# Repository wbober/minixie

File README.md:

minixie
=======

This project is my take on creating a simple Nixie tube clock. The design uses few
components but packs some nice features.

Features
--------
* a real time clock with super cap backup
* a buzzer
* a light intensity sensor
* an auxiliary connector (UART, IRQ, GPIO, +5V)
* support for an optional DCF77 decoder

Hardware
--------
* only 3 ICs (7805, ATMega8, and 74141 driver)
* single side PCBs
* through-hole components
* designed for LC531 tubes
* small size (46x108mm)
* EagleCAD source for schematics and PCB

Software
--------
* written in C
* tested with AVRStudio/Eclipse

License
-------
Copyright (c) 2012-2014 Wojciech Bober
Licensed under the GNU GPL v2 license

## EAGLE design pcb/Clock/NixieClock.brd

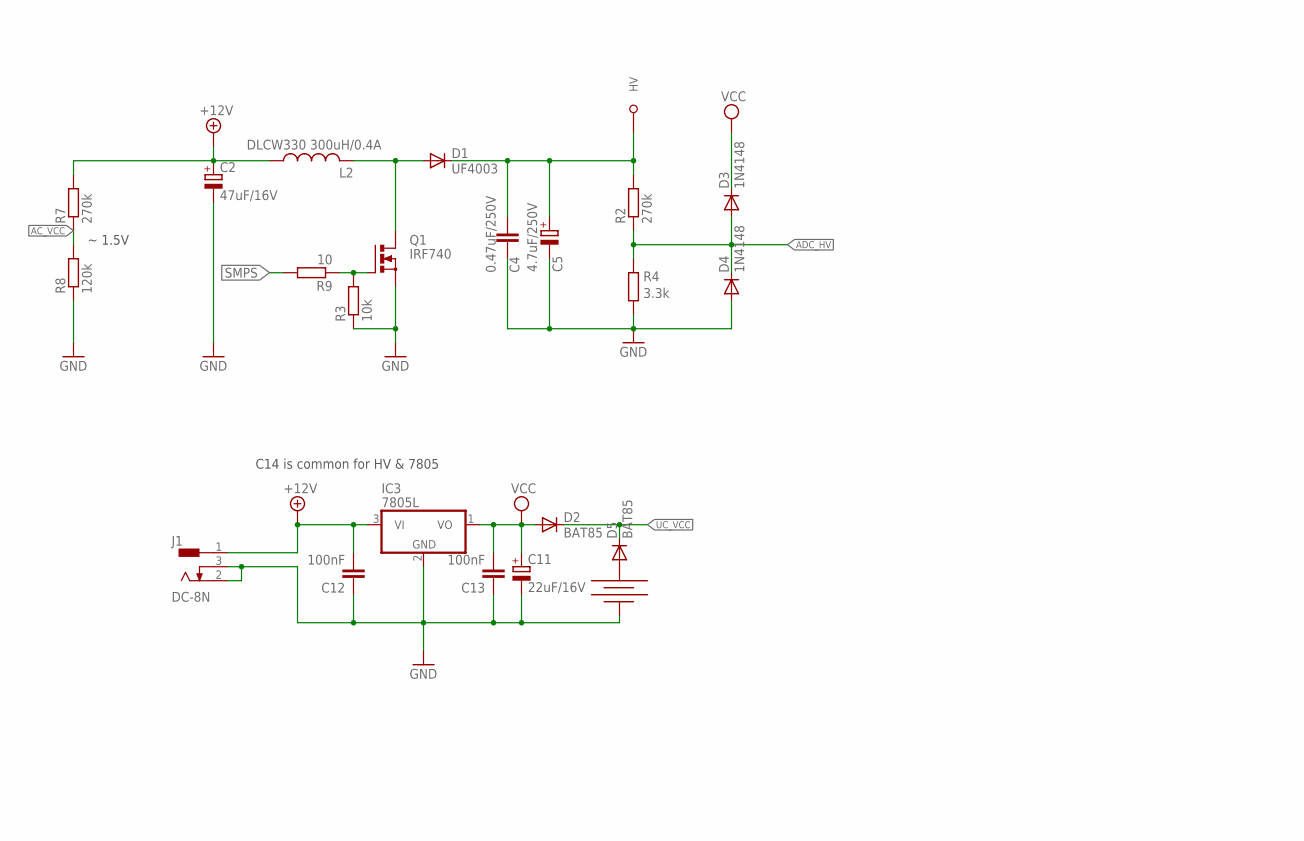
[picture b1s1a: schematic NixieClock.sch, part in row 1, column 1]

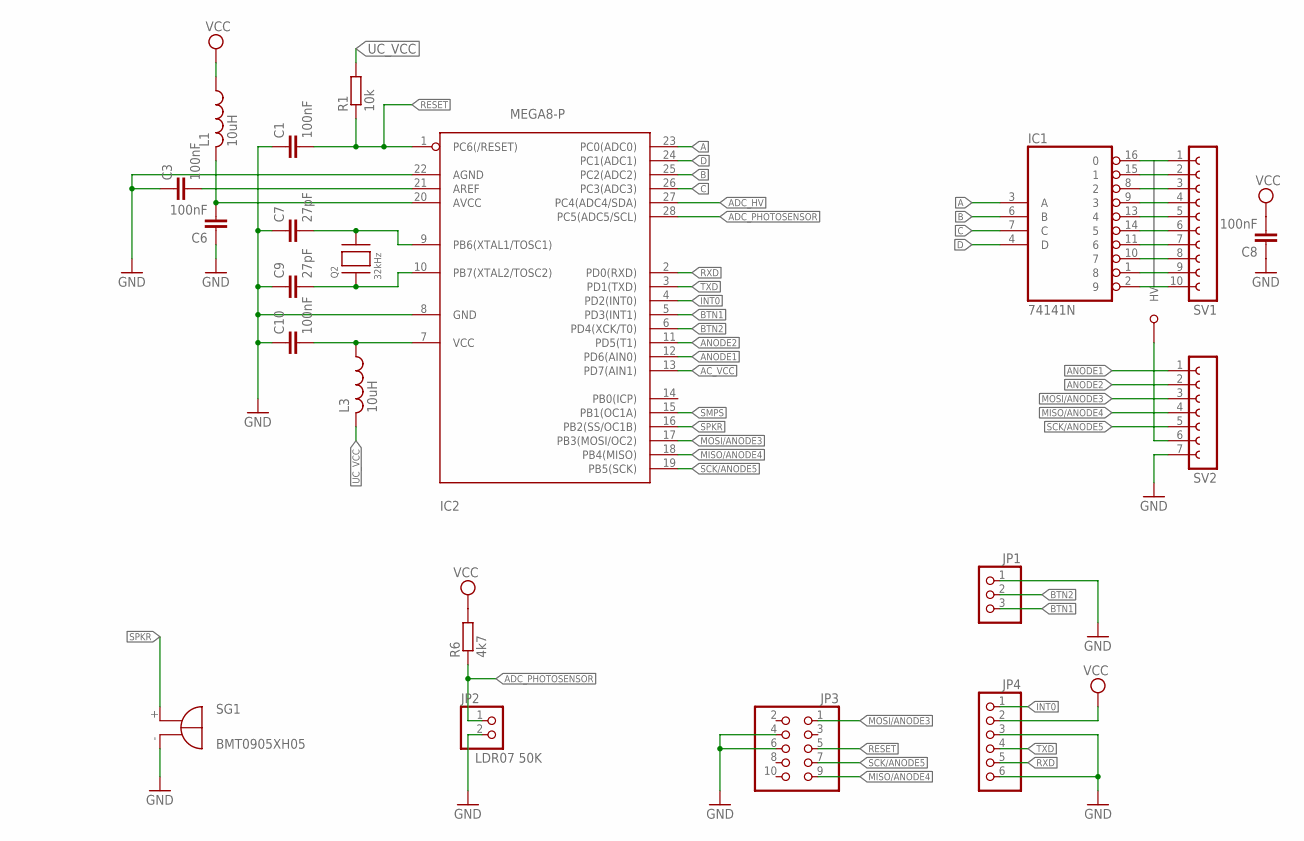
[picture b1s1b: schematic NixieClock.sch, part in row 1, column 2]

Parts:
C1, C3, C6, C10, C12, C13: 100nF; C025-025X050
C2: 47uF/16V; E2,5-7
C4: 0.47uF/250V; C10B6
C5: 4.7uF/250V; CAP_RADIAL
C7, C9: 27pF; C025-025X050
C8: 100nF; C050-025X075
C11: 22uF/16V; E2,5-6
D1: UF4003; DO41-10
D2, D5: BAT85; DO35-7
D3, D4: 1N4148; DO35-7
IC1: 74141N; DIL16
IC2: MEGA8-P; DIL28-3
IC3: 7805L; TO92
J1: DC-8N
JP1: PINHD-1X3/90; 1X03/90
JP2: LDR07 50K; 1X02
JP3: PINHD-2X5/90; 2X05/90
JP4: PINHD-1X6/90; 1X06/90
L1: 10uH; 0204/7
L2: DLCW330 300uH/0.4A; MURATA-CHOKE-7-4
L3: 10uH; 0204/5
Q1: IRF740; TO220BH
Q2: 32kHz; QS
R1: 10k; 0207/12
R2, R7: 270k; 0204/5
R3: 10k; 0204/5
R4: 3.3k; 0204/5
R6: 4k7; 0204/5
R8: 120k; 0204/5
R9: 10; 0204/5
SG1: BMT0905XH05
SV1: FE10-1; FE10
SV2: FE07-1; FE07
U$3: BAT1220THT; 1220

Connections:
+12V: C2.+, C12.2, IC3.3 (VI), J1.1, L2.P$1 (1), R7.2
A: IC1.3 (A), IC2.23 (PC0(ADC0))
AC_VCC: IC2.13 (PD7(AIN1)), R7.1, R8.2
ADC_HV: D3.A, D4.C, IC2.27 (PC4(ADC4/SDA)), R2.1, R4.2
ADC_PHOTOSENSOR: IC2.28 (PC5(ADC5/SCL)), JP2.1, R6.1
ANODE1: IC2.12 (PD6(AIN0)), SV2.1
ANODE2: IC2.11 (PD5(T1)), SV2.2
B: IC1.6 (B), IC2.25 (PC2(ADC2))
BTN1: IC2.5 (PD3(INT1)), JP1.3
BTN2: IC2.6 (PD4(XCK/T0)), JP1.2
C: IC1.7 (C), IC2.26 (PC3(ADC3))
D: IC1.4 (D), IC2.24 (PC1(ADC1))
D1: IC1.2 (9), SV1.1
D2: IC1.1 (8), SV1.2
D3: IC1.16 (0), SV1.3
D4: IC1.15 (1), SV1.4
D5: IC1.14 (5), SV1.5
D6: IC1.13 (4), SV1.6
D7: IC1.11 (6), SV1.7
D8: IC1.10 (7), SV1.8
D9: IC1.9 (3), SV1.9
D10: IC1.8 (2), SV1.10
GND: C1.1, C2.-, C3.1, C4.2, C5.P$4 (-), C6.1, C7.1, C8.1, C9.1, C10.1, C11.-, C12.1, C13.1, D4.A, IC1.12 (GND), IC2.8 (GND), IC2.22 (AGND), IC3.2 (GND), J1.2, J1.3, JP1.1, JP2.2, JP3.4, JP3.6, JP4.3, JP4.6, Q1.S, R3.1, R4.1, R8.1, SG1.-, SV2.7, U$3.-
HV: C4.1, C5.P$3 (+), D1.C, R2.2, SV2.6
INT0: IC2.4 (PD2(INT0)), JP4.1
MISO/ANODE4: IC2.18 (PB4(MISO)), JP3.9, SV2.4
MOSI/ANODE3: IC2.17 (PB3(MOSI/OC2)), JP3.1, SV2.3
unnamed: C7.2, IC2.9 (PB6(XTAL1/TOSC1)), Q2.P$2
unnamed: C9.2, IC2.10 (PB7(XTAL2/TOSC2)), Q2.P$1
unnamed: D5.A, U$3.+
unnamed: Q1.G, R3.2, R9.1
unnamed: C6.2, IC2.20 (AVCC), L1.2
unnamed: C10.2, IC2.7 (VCC), L3.1
unnamed: C3.2, IC2.21 (AREF)
unnamed: D1.A, L2.P$2 (2), Q1.D
RESET: C1.2, IC2.1 (PC6(/RESET)), JP3.5, R1.1
RXD: IC2.2 (PD0(RXD)), JP4.5
SCK/ANODE5: IC2.19 (PB5(SCK)), JP3.7, SV2.5
SMPS: IC2.15 (PB1(OC1A)), R9.2
SPKR: IC2.16 (PB2(SS/OC1B)), SG1.+
TXD: IC2.3 (PD1(TXD)), JP4.4
UC_VCC: D2.C, D5.C, L3.2, R1.2
VCC: C8.2, C11.+, C13.2, D2.A, D3.C, IC1.5 (VCC), IC3.1 (VO), JP4.2, L1.1, R6.2

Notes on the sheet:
C14 is common for HV & 7805
~ 1.5V

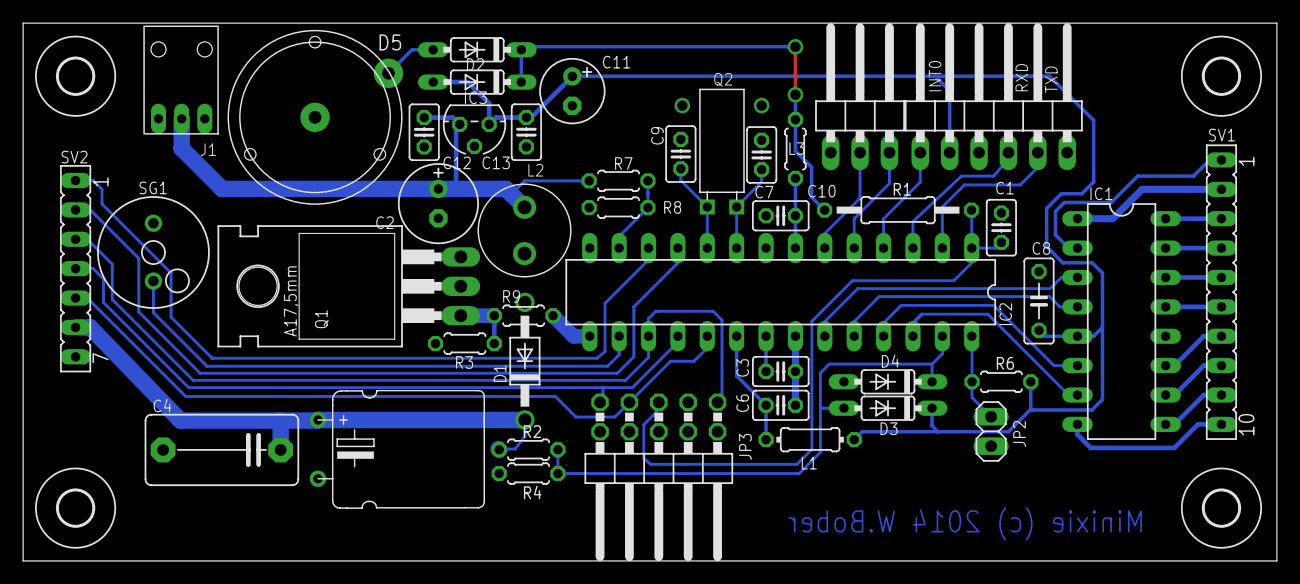
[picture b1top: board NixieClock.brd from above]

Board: 2 copper layers, 108.4 x 46.5 mm, 47 parts (0 on the bottom side), 43 nets.

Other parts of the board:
U$5, U$6, U$7, U$8: 3,0

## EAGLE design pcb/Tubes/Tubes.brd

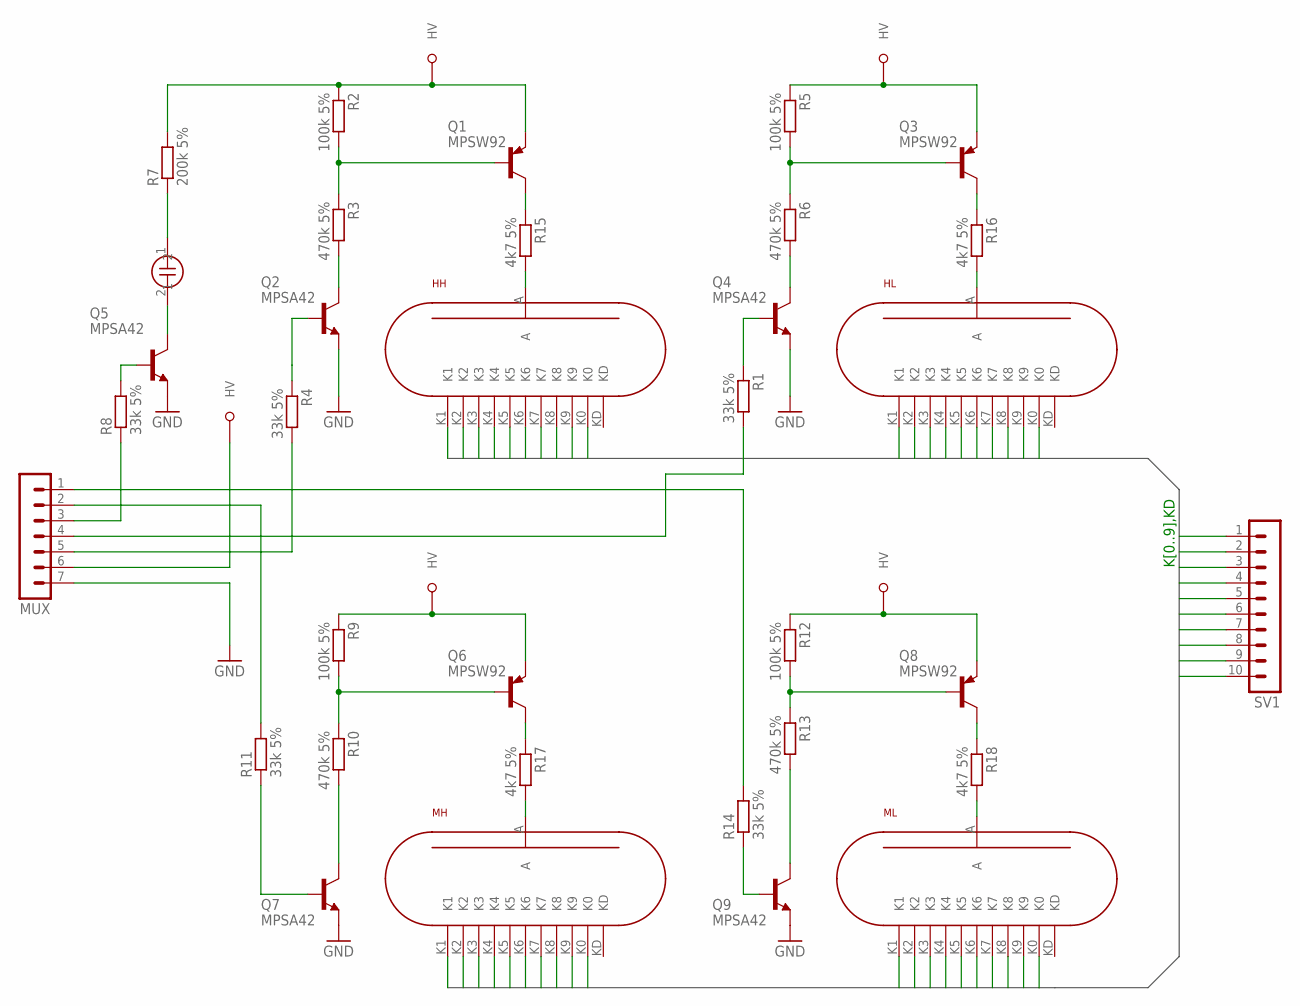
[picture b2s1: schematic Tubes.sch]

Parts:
HH: LC531
HL: LC531
MH: LC531
ML: LC531
MUX: MA07-1
NEON: NEON
Q1, Q3, Q6, Q8: MPSW92; TO92-CBE
Q2, Q4, Q5, Q7, Q9: MPSA42; TO92-CBE
R1, R4, R8, R11, R14: 33k 5%; 0204/5
R2, R5, R9, R12: 100k 5%; 0204/5
R3, R6, R10, R13: 470k 5%; 0204/5
R7: 200k 5%; 0204/5
R15, R16, R17, R18: 4k7 5%; 0204/5
SV1: MA10-1

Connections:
DOT: MUX.3, R8.1
GND: MUX.7, Q2.E, Q4.E, Q5.E, Q7.E, Q9.E
HH: MUX.5, R4.2
HL: MUX.4, R1.2
HV: MUX.6, Q1.E, Q3.E, Q6.E, Q8.E, R2.1, R5.1, R7.2, R9.1, R12.1
K0: HH.K0, HL.K0, MH.K0, ML.K0, SV1.3
K1: HH.K1, HL.K1, MH.K1, ML.K1, SV1.1
K2: HH.K2, HL.K2, MH.K2, ML.K2, SV1.2
K3: HH.K3, HL.K3, MH.K3, ML.K3, SV1.4
K4: HH.K4, HL.K4, MH.K4, ML.K4, SV1.6
K5: HH.K5, HL.K5, MH.K5, ML.K5, SV1.8
K6: HH.K6, HL.K6, MH.K6, ML.K6, SV1.10
K7: HH.K7, HL.K7, MH.K7, ML.K7, SV1.9
K8: HH.K8, HL.K8, MH.K8, ML.K8, SV1.7
K9: HH.K9, HL.K9, MH.K9, ML.K9, SV1.5
MH: MUX.2, R11.2
ML: MUX.1, R14.2
unnamed: MH.A, R17.2
unnamed: ML.A, R18.2
unnamed: HH.A, R15.2
unnamed: HL.A, R16.2
unnamed: Q1.C, R15.1
unnamed: Q3.C, R16.1
unnamed: Q6.C, R17.1
unnamed: Q8.C, R18.1
unnamed: NEON.1, R7.1
unnamed: Q2.B, R4.1
unnamed: Q4.B, R1.1
unnamed: Q7.B, R11.1
unnamed: Q9.B, R14.1
unnamed: Q2.C, R3.2
unnamed: Q7.C, R10.2
unnamed: Q9.C, R13.2
unnamed: Q4.C, R6.2
unnamed: NEON.2, Q5.C
unnamed: Q1.B, R2.2, R3.1
unnamed: Q3.B, R5.2, R6.1
unnamed: Q6.B, R9.2, R10.1
unnamed: Q8.B, R12.2, R13.1
S$1: Q5.B, R8.2

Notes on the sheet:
K[0..9],KD

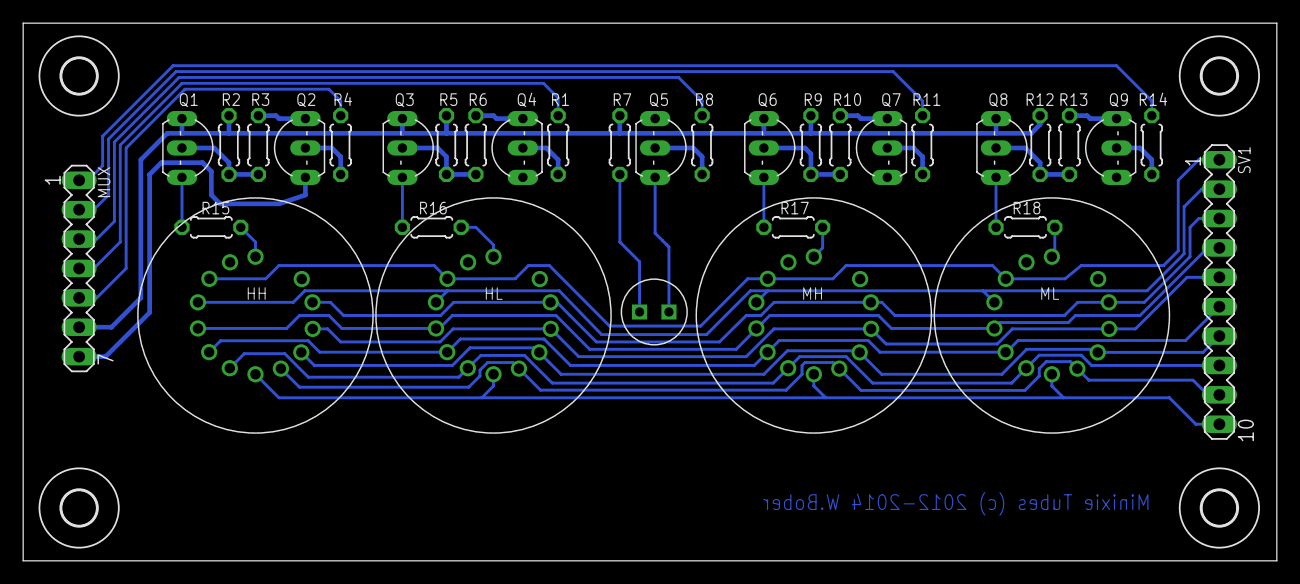
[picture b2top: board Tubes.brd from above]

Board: 2 copper layers, 108.4 x 46.5 mm, 38 parts (0 on the bottom side), 40 nets.

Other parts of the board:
E$1, E$2, E$3, E$4: 3,0

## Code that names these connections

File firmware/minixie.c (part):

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
/* 
 * Anode mapping table:
 * HH -> PB5
 * HL -> PB4
 * MH -> PD5
 * ML -> PD6
 * DOT -> PB3
 */
static const pad_t const anode_pad_map[] = {
	PAD(&PORTB, 5),
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
volatile static ctx_t ctx = {
	.tick = 1,
	.dot = 1,
	.debug = 0,
	.beep = 0,
	.dcf_sync_cnt = 0,
	.duty_cycle = SMPS_PWM_DC,
	.dot_pwm = 0,
	.digit = {0},
	.adc_hv = 0,
	.adc_light = 0,
	.alarm = {255},
};
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static void hw_init(void)
{
	// set the anode pins as an output
	DDRB = _BV(PB2) | _BV(PB3) | _BV(PB4) | _BV(PB5);
	DDRD = _BV(PD5) | _BV(PD6);
	// set the digit pins as an output
	DDRC = _BV(PC0) | _BV(PC1) | _BV(PC2) | _BV(PC3);
	
	// enable pull-ups on button inputs
	PORTD = _BV(PD3) | _BV(PD4);
	
	// Enable IRQ0 on PD2 
	MCUCR |= _BV(ISC00);
	GICR |= _BV(INT0);

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	// (note: for inverting add _BV(COM1A0))
	TCCR1A = _BV(WGM11) | _BV(COM1A1);
	TCCR1B = _BV(WGM13) | _BV(WGM12);
	DDRB |= _BV(PB1);

	ICR1 = SMPS_PWM_PERIOD;
	OCR1A = (ctx.duty_cycle*SMPS_PWM_PERIOD)/100;
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{
	ctx.poll = 1;
	ctx.tick = 1;
	ctx.dot ^= 1;
	
	if (ctx.time.ss < 59) {
		ctx.time.ss++;
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
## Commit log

2014-12-21 Replaced backup capacitor with a CR1220 battery holder.
2015-10-10 Enabled minutes button
2015-10-10 Added hex file to bin/minixie.hex
2015-10-10 Added screenshot of fuse bits settings
2015-10-14 Enable or disable adaptive dc using ADAPTIVE_DC macro definition
2015-10-14 Enable pull-ups on PD3 and PD4 (BTN1 and BTN2)
2016-08-22 Updated firmware file
2016-08-23 Changed MOSFET from IRF710 to IRF740. Added part number for inductor
2016-08-23 Added part number for photoresistor

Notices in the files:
firmware/minixie.c:
This program is free software; you can redistribute it and/or modify
it under the terms of the GNU General Public License as published by
the Free Software Foundation; either version 2 of the License, or
(at your option) any later version.
pcb/Clock/NixieClock.brd:
Minixie (c) 2014 W.Bober
pcb/Tubes/Tubes.brd:
Minixie Tubes (c) 2012-2014 W.Bober
